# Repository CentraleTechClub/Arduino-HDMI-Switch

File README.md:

# Arduino-controlled HDMI switch - KiCad 10

# Sponsors wanted: help CentraleTech fabricate this PCB

**CentraleTech is looking for sponsors to fund PCB fabrication for this project. Your support will help us manufacture and test the board. Interested in sponsoring us? Please contact CentraleTech through our GitHub profile.**

Open Arduino-HDMI-Switch.kicad_pro, then its PCB or schematic.
This is a revised version of the supplied HDMI-Off board. A 5 V DPDT relay,
driven by an AO3400A MOSFET, replaces the manual switch. The Arduino GPIO
drives only the MOSFET gate; the relay coil runs from the 5 V supply.

## Wiring

Connect HDMI source to J1 and display to J2.
J3 pad 1 (square pad): Arduino regulated 5 V.
J3 pad 2: Arduino control GPIO, for example D8.
J3 pad 3: Arduino GND.
Use the PCB pad numbers: the older Prototype folder has a different pinout.
HIGH enables HDMI +5 V and Hot Plug Detect; LOW, floating control, or loss
of relay supply opens both relay contacts. Use a regulated 5 V supply for
the coil, not a GPIO or the Arduino VIN pin. 3.3 V or 5 V control is supported.
The coil supply must accommodate the selected relay's datasheet current.

## Design and assembly

K1: Omron G5V-2-H1 DC5, 5 V DPDT, Relay_DPDT_Omron_G5V-2 footprint.
Use the specified pinout and 5 V coil; check any substitute against its datasheet.
Q1: AO3400A in SOT-23; D3: 1N4148W in SOD-123, cathode toward +5 V.
D2: PMEG2010EA in SOD-323; D1: 3 mm green LED.
R1: 1.5 kohm; R2: 1 kohm; R3: 100 kohm, all 0805.
C1: 100 nF / 16 V; C2: 10 uF / 16 V, ceramic 0805.
J1/J2 retain the original HDMI footprint, bundled in HDMI_Switch.pretty.
Confirm the sockets you purchase match it. J3 is a 2.54 mm 3-pin header.
The board has FOUR copper layers and nominal 1.6 mm thickness.
Do not order it as a two-layer board.

## Checks performed

KiCad 10.0.8 ERC: 0 reported violations.
KiCad DRC after zone refill: 0 reported violations, 0 unconnected items,
and 0 PCB/schematic parity issues. See reports/ for the actual results.
Minimum copper clearance is 0.15 mm; copper-to-edge clearance is 0.25 mm.
The top board edge was extended by 0.1 mm to clear the existing clock trace.
All 168 original TMDS/DDC/CEC tracks, arcs and vias were compared and
preserved. The relay switches only HDMI pins 18 (+5 V) and 19 (HPD).
Gerbers and separate plated/nonplated drill files were regenerated from
this checked board. Silkscreen exports subtract solder-mask openings.
The project footprint paths now use KiCad's portable library variable.

The inherited project ignores missing courtyards, off-center via endpoints,
footprint filters, silk-over-mask, PTH/NPTH-inside-courtyard, and tuning
profile geometry checks; the DRC report lists these explicitly. Connectivity,
shorts and copper clearance checks are enabled. No individual DRC exclusions
are used. ERC also retains the ignored informational checks listed in ERC.json.

## Limits and first test

This is a CAD-checked design, not a physically tested unit. HDMI signal
integrity and operation at a particular resolution/refresh rate have not been
measured. The inherited stack-up is not a verified 100-ohm impedance design;
confirm its suitability with the board manufacturer before ordering for a
specific high-speed HDMI mode. Pin 14 remains unconnected as in the original;
ARC/eARC/HEC are not supported. Opening +5 V and HPD reproduces the original
switch function, but a guaranteed video blackout depends on source/display
behavior. No high-speed data lanes are disconnected.

Before connecting equipment, inspect soldering and check for power shorts.
With the Arduino supply on and HDMI cables disconnected, toggle D8 and check
that K1 pins 4-8 and 13-9 are open at LOW and closed at HIGH. D2 is in series
with HDMI +5 V, so use diode mode when checking that complete path.
Then test with an inexpensive HDMI source/display before valuable equipment.
The included .ino is a manual serial-command test: send 1 for ON, 0 for OFF.

## Files

- Arduino-HDMI-Switch.kicad_pro / .kicad_sch / .kicad_pcb: editable project.
- fabrication/: Gerbers, drill files and Gerber job.
- BOM.csv: assembly parts.
- reports/: KiCad ERC/DRC and independent connection listing.
- routing.svg: current layer preview. Existing PNG images are earlier previews.

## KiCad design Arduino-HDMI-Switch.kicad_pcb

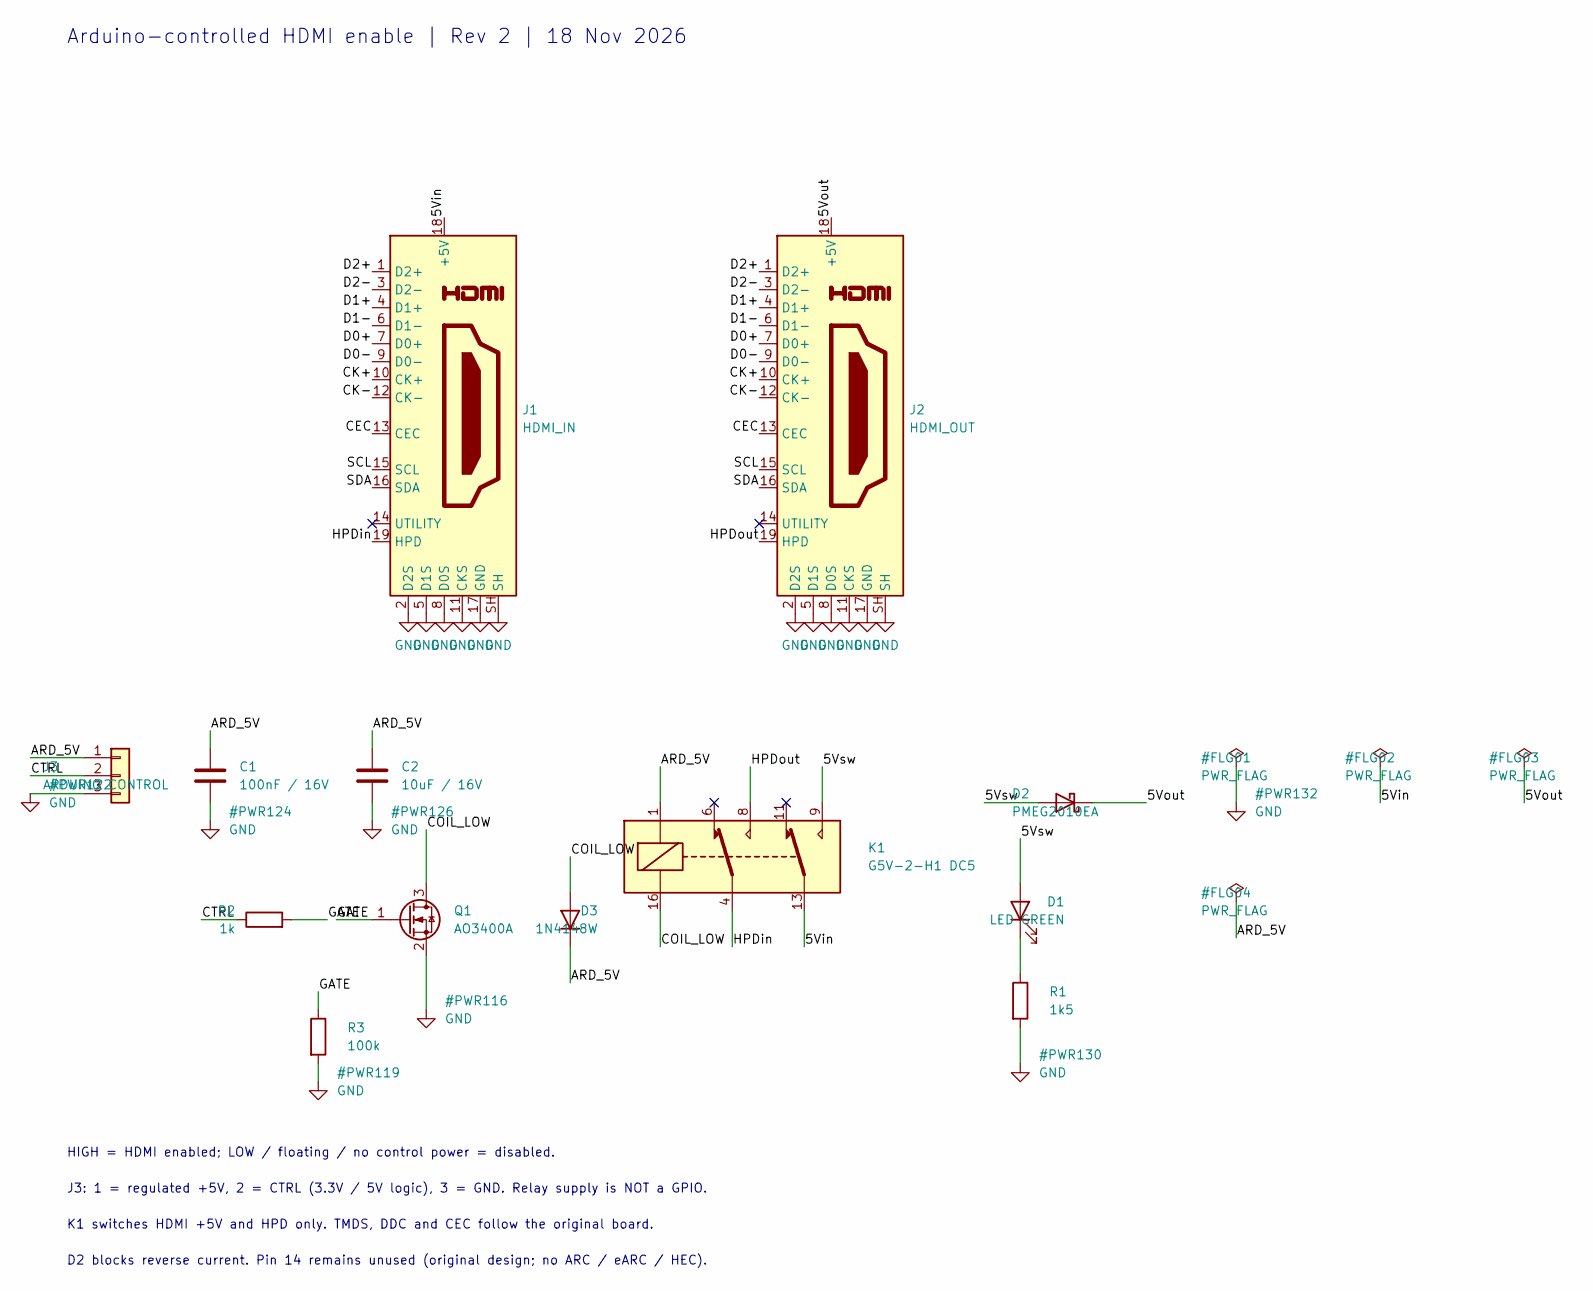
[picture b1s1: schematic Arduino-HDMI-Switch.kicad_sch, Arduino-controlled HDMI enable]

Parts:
C1: 100nF / 16V; C_0805_2012Metric_Pad1.18x1.45mm_HandSolder
C2: 10uF / 16V; C_0805_2012Metric_Pad1.18x1.45mm_HandSolder
D1: LED GREEN; LED_D3.0mm
D2: PMEG2010EA; D_SOD-323
D3: 1N4148W; D_SOD-123
J1: HDMI_IN; HDMI_TE_1747981-2; LCSC C138388
J2: HDMI_OUT; HDMI_TE_1747981-2; LCSC C138388
J3: ARDUINO CONTROL; PinHeader_1x03_P2.54mm_Vertical
K1: G5V-2-H1 DC5; Relay_DPDT_Omron_G5V-2
Q1: AO3400A; SOT-23
R1: 1k5; R_0805_2012Metric_Pad1.20x1.40mm_HandSolder
R2: 1k; R_0805_2012Metric_Pad1.20x1.40mm_HandSolder
R3: 100k; R_0805_2012Metric_Pad1.20x1.40mm_HandSolder

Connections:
/5Vin: J1.18 (+5V), K1.13
/5Vout: D2.1 (K), J2.18 (+5V)
/5Vsw: D1.2 (A), D2.2 (A), K1.9
/ARD_5V: C1.1, C2.1, D3.1 (K), J3.1, K1.1
/CEC: J1.13 (CEC), J2.13 (CEC)
/CK+: J1.10 (CK+), J2.10 (CK+)
/CK-: J1.12 (CK-), J2.12 (CK-)
/COIL_LOW: D3.2 (A), K1.16, Q1.3 (D)
/CTRL: J3.2, R2.1
/D0+: J1.7 (D0+), J2.7 (D0+)
/D0-: J1.9 (D0-), J2.9 (D0-)
/D1+: J1.4 (D1+), J2.4 (D1+)
/D1-: J1.6 (D1-), J2.6 (D1-)
/D2+: J1.1 (D2+), J2.1 (D2+)
/D2-: J1.3 (D2-), J2.3 (D2-)
/GATE: Q1.1 (G), R2.2, R3.1
/HPDin: J1.19 (HPD), K1.4
/HPDout: J2.19 (HPD), K1.8
/SCL: J1.15 (SCL), J2.15 (SCL)
/SDA: J1.16 (SDA), J2.16 (SDA)
GND: C1.2, C2.2, J1.2 (D2S), J1.5 (D1S), J1.8 (D0S), J1.11 (CKS), J1.17 (GND), J1.SH, J2.2 (D2S), J2.5 (D1S), J2.8 (D0S), J2.11 (CKS), J2.17 (GND), J2.SH, J3.3, Q1.2 (S), R1.2, R3.2
unnamed: D1.1 (K), R1.1

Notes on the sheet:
Arduino-controlled HDMI enable | Rev 2 | 18 Nov 2026
HIGH = HDMI enabled; LOW / floating / no control power = disabled.
J3: 1 = regulated +5V, 2 = CTRL (3.3V / 5V logic), 3 = GND. Relay supply is NOT a GPIO.
K1 switches HDMI +5V and HPD only. TMDS, DDC and CEC follow the original board.
D2 blocks reverse current. Pin 14 remains unused (original design; no ARC / eARC / HEC).

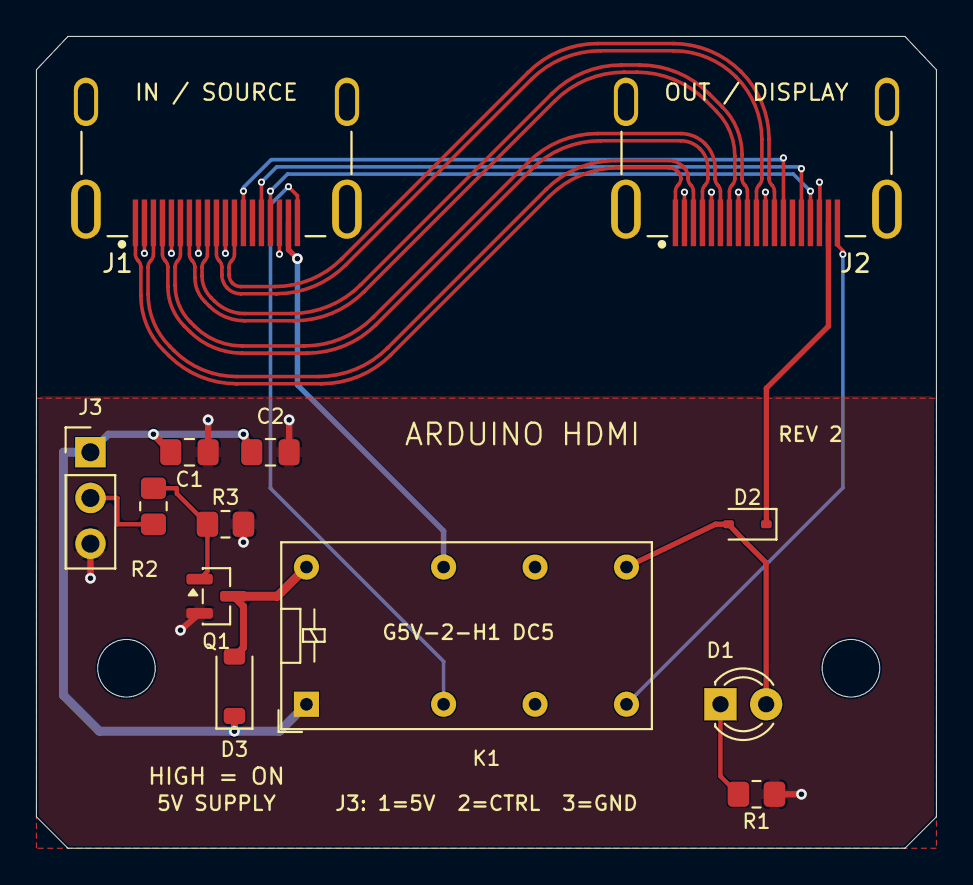
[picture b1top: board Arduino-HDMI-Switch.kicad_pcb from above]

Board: 4 copper layers, 50.0 x 45.1 mm, 15 parts (0 on the bottom side), 22 nets.

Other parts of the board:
MH1, MH2: MountingHole_3.2mm_M3

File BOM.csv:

Reference,Value,Footprint
K1,G5V-2-H1 DC5,Relay_THT:Relay_DPDT_Omron_G5V-2
Q1,AO3400A,Package_TO_SOT_SMD:SOT-23
R2,1k,Resistor_SMD:R_0805_2012Metric_Pad1.20x1.40mm_HandSolder
R3,100k,Resistor_SMD:R_0805_2012Metric_Pad1.20x1.40mm_HandSolder
D3,1N4148W,Diode_SMD:D_SOD-123
J3,ARDUINO CONTROL,Connector_PinHeader_2.54mm:PinHeader_1x03_P2.54mm_Vertical
C1,100nF / 16V,Capacitor_SMD:C_0805_2012Metric_Pad1.18x1.45mm_HandSolder
C2,10uF / 16V,Capacitor_SMD:C_0805_2012Metric_Pad1.18x1.45mm_HandSolder
D2,PMEG2010EA,Diode_SMD:D_SOD-323
D1,LED GREEN,LED_THT:LED_D3.0mm
R1,1k5,Resistor_SMD:R_0805_2012Metric_Pad1.20x1.40mm_HandSolder
J1,HDMI_IN,HDMI_Switch:HDMI_TE_1747981-2
J2,HDMI_OUT,HDMI_Switch:HDMI_TE_1747981-2
